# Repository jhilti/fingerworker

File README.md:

# Fingerworker

**[R31 mit Rev E in 3D ansehen →](https://fingerworker-development-notebook.jonashilti.chatgpt.site/#cad-r31-rev-e)** · [R20-3D-Archiv](https://jhilti.github.io/fingerworker/)

Ein 3D-gedruckter Prototyp für Fingerkrafttraining mit federgeführtem Griff, organischer Handballenauflage und optionaler Kraftmessung. Dieses Repository enthält CAD-Quellen, Firmware, eine iPhone-App, Elektronikentwurf und die Entwicklungshistorie.

*A 3D-printed finger-training prototype with a spring-loaded grip and optional force sensing. The latest documented assembly is Flat132 R31 with Rev E electronics.*

## R31 mit Rev‑E‑Elektronik

**Stand 25.11.2026.** Das vollständige R31-Modell zeigt den Federbetrieb in Ruhestellung mit flacher Handauflage, fester Sensorhaltnase, FX1901-Kraftsensor, Fingerschlitten, Akku und USB-C-Zugang von oben. Je ein verdrahteter Daumentaster sitzt links und rechts am Querbalken. Beide teilen sich den Eingang D7 über J4. Im iOS-Basistraining löst ein kurzer Druck einen Handwechsel aus.

Schaltplan- und Layoutprüfung in KiCad sowie Firmware- und iOS-Build sind abgeschlossen. Passung, Bediengefühl und Handwechsel per Bluetooth stehen am verdrahteten Muster noch zur Prüfung aus.

[Vollständige Baugruppe in Onshape](https://cad.onshape.com/documents/15316cc6370631845af136b2/w/8b79384f95b34ba58197ab08/e/061a7997871e238371c40026) · [Entwicklungsnotizbuch mit drehbarem 3D-Modell](https://fingerworker-development-notebook.jonashilti.chatgpt.site/#cad-r31-rev-e)

## Die App

Screenshots aus dem iOS-Simulator mit simulierten Testdaten.

| Training | Messung | Einstellungen |
| --- | --- | --- |
|  |  |  |
| Geführte Sätze und Handwechsel. | Kraftverlauf und Messwerte. | Trainingsart, Umfang und Pausen. |

## Modell ansehen

- **[R20-3D-Ansicht direkt öffnen](https://jhilti.github.io/fingerworker/)** – öffentliche interaktive Ansicht zum Teilen.
- [R20-3D-Ansicht als HTML](share/Fingerworker_R20_3D.html) – herunterladen und offline im Browser öffnen. GitHub zeigt die HTML-Datei auf der Repository-Seite als Quelltext an.
- [Projektübersicht](Uebersicht.html) – lokale Übersicht mit Modell und Dokumentation. Für ihre relativen Verweise das Repository herunterladen.
- [Onshape R20, unveränderliche Version](https://cad.onshape.com/documents/15316cc6370631845af136b2/v/0e06e3d98b9ecb574ee41402/e/d253eb87b70818ebde8215f0) – nativer CAD-Stand des R20-Releases.
- [Release v0.20.0-prototype](https://github.com/jhilti/fingerworker/releases/tag/v0.20.0-prototype) – native CAD-Downloads und Veröffentlichungsstand.

## Veröffentlichter Prototypstand R20

<!-- CURRENT_FLAT132_R20_START -->

Die hinteren Halter P06L und P06R sind separate massive Blöcke. Je ein integrierter **Ø5 × 2 mm Positionierzapfen** gleitet beim axialen Aufschieben in eine hinten offene Nut der Grundplatte. Das ermöglicht einen **federfreien, unbelasteten Passaufbau ohne Schrauben**. Die organische Handballenauflage, beidseitigen Daumenmulden und Durchlässe für zwei 25-mm-Gurte bleiben erhalten. Es gibt keine Vorspannverstellung.

**Vor jeder Federlast, auch der Vorspannung in Ruhestellung, sind vier M3×8-Schrauben in den vorgesehenen Inserts erforderlich.** Die Zapfen verriegeln die Blöcke nicht gegen Herausziehen. R20-Grundplatte und beide R20-Halter gemeinsam verwenden; [Montageanleitung beachten](review/rear-locating-pegs-2026-11-13/MONTAGE.md).

Nominale CAD-Prüfungen sind dokumentiert. Reale Druckpassung, Komfort, Elektronik, Kalibrierung und belastete Funktion bleiben zu prüfen. Es gibt keine validierte Lastfreigabe oder klinische Freigabe; frühere Kraftziele sind keine geprüften Belastbarkeitsangaben.

**Druckvorbereitung pausiert:** PLA ist das vorgesehene Standardmaterial. Für R20 existieren noch kein freigegebenes Bambu-Projekt und kein neuer Slice. Ältere Druckpakete bilden frühere Revisionen ab und enthalten die R20-Änderungen nicht.

<!-- CURRENT_FLAT132_R20_END -->

## CAD herunterladen

- [Native STL-Baugruppe: Flat132_R20_neutral_final.zip](https://github.com/jhilti/fingerworker/releases/download/v0.20.0-prototype/Flat132_R20_neutral_final.zip)
- [Native STEP-Baugruppe: Flat132_R20_final_AP214.step](https://github.com/jhilti/fingerworker/releases/download/v0.20.0-prototype/Flat132_R20_final_AP214.step)
- [FeatureScript-Quelle](fingerworker_mvp.fs) · [R20-Änderungsbericht](review/rear-locating-pegs-2026-11-13/README.md) · [Prüfbindung](review/rear-locating-pegs-2026-11-13/final-specification.json)

Die native STL-Baugruppe enthält auch Referenzhardware und ist kein fertig angeordnetes Druckprojekt. Für lokale Modell-Builds stellt der Download-Helfer das unveränderte ZIP am erwarteten Projektpfad wieder her:

```sh
python3 tools/download_release_assets.py
```

Details stehen in [Veröffentlichung und Wiederherstellung](PUBLISHING.md).

Weitere Downloads im selben Release:

- [R20-3D-Ansicht als ZIP](https://github.com/jhilti/fingerworker/releases/download/v0.20.0-prototype/Fingerworker_R20_3D.zip) – eigenständige HTML-Datei zum Weitergeben.
- [Historische Bambu-Projekte bis R18](https://github.com/jhilti/fingerworker/releases/download/v0.20.0-prototype/Historical_Bambu_Projects_through_R18.zip) – 24 bestehende 3MF-Dateien, ausschließlich historische Stände; **kein R20-Druckpaket**.
- [Historische Metallzeichnungen Rev A](https://github.com/jhilti/fingerworker/releases/download/v0.20.0-prototype/Historical_Mechanical_Drawings_RevA.zip).
- [Technische Elektronikexporte Rev A](https://github.com/jhilti/fingerworker/releases/download/v0.20.0-prototype/Electronics_RevA_Technical_Exports.zip) – dokumentierter Entwicklungsstand, keine Fertigungsfreigabe.

## Projektbereiche

| Bereich | Inhalt |
| --- | --- |
| [Mechanik und Montage](review/rear-locating-pegs-2026-11-13/README.md) | R20-Geometrie, Positionierzapfen, Passungen und nominale Prüfungen |
| [Stückliste](EINKAUFSTEILE.md) | Bauteile, Befestigungen und Revisionshinweise |
| [Firmware](firmware/README.md) | Kraftmessung, Endschalter, BLE und lokale Test-/Build-Werkzeuge |
| [iPhone-App](ios/README.md) | BLE-Anbindung, Trainingsansicht und Sitzungsspeicherung |
| [Elektronik](electronics/kicad/README.md) | KiCad-Schaltplan, Platine und dokumentierter Entwurfsstand |
| [Spezifikation](SPECIFICATION.md) / [offene Arbeiten](GAP_ANALYSIS.md) | Anforderungen und noch ausstehende Hardware-Nachweise |
| [Druckstatus](print/REVISION_STATUS.md) | Zuordnung früherer Druckstände; R20-Druckvorbereitung pausiert |

Firmware, App und Elektronik sind Teil des Prototyps. Eine dokumentierte Softwareprüfung ersetzt keine elektrische oder mechanische Qualifikation des aufgebauten Geräts. Bei historischen Dokumenten gilt die jeweils genannte Revision.

## Umfang der Veröffentlichung

Quellen und technische Entwicklungshistorie bleiben erhalten. Persönliche Bestellungen und Scans, Studien mit persönlichen Referenzen, Laufzeitumgebungen, Hersteller-PDFs/-CAD sowie alte generierte Spiegelkopien sind aus dem öffentlichen Repository ausgenommen. Historische Dokumente können deshalb auf nur lokal vorhandene Dateien verweisen. Details und CAD-Wiederherstellung stehen in [PUBLISHING.md](PUBLISHING.md).

Für die eigenen Projektdateien wurde noch keine Open-Source-Lizenz gewählt. Die Veröffentlichung allein erteilt keine solche Lizenz; gegebenenfalls enthaltene Drittbestandteile behalten ihre jeweiligen Lizenzbedingungen.

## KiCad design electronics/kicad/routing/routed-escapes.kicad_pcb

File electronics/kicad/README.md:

# Fingerworker – KiCad, Revision A

11. Oktober 2026. **Geroutetes, editierbares Prototypenprojekt Rev A-P1 für KiCad 10.0.6**, abgeglichen mit `electronics/order/RevA-P1-JLC/source/`. C4 und C7: jeweils **22 µF**, Murata **GRM21BR61E226ME44L**, 25 V, X5R, 0805. Schaltpläne, PCB, lokale Symbolbibliothek und native Pin-/Netzdaten entsprechen dieser eingefrorenen JLC-Quelle. Routing und Bauteilpositionen sind unverändert.

Die separat freigegebenen YAGEO-Ersatzteile für C5/C6/C13 bleiben im JLC-Portal-BOM und in `../order/RevA-P1-JLC/SUBSTITUTIONS.md` dokumentiert; die eingefrorene Quell-BOM enthält deren ursprüngliche Murata-MPNs. Für Portal-Uploads gilt `BOM_JLC_portal.csv`.

Frische ERC-/DRC-Prüfung einschließlich Schaltplanabgleich: keine Fehler, Warnungen oder offenen Verbindungen. Hardwarefunktion und Gehäuseintegration bleiben am Muster zu prüfen. USB-Erkennung der Firmware verwendet jetzt den internen VBUS-Detektor statt des D6-Teilers.

## Öffnen

`Fingerworker_RevA.kicad_pro` in KiCad öffnen; Schaltplan und PCB über den Projektmanager starten. Symbol- und Footprint-Bibliotheken sind lokal enthalten. Unter `preview/` liegen alle vier Schaltplanblätter, beide PCB-Seiten und die lokale Bauraumstudie als SVG/PNG.

## Platine

- **19,5 × 68,5 × 0,8 mm**, vier Kupferlagen, ausschließlich Bestückung oben.
- 48 Footprints, 51 Schaltplansymbole einschließlich externem Sensor, Akku und Endschalter.
- F.Cu: Bauteile, kurze Mess- und Schaltreglerwege. In1.Cu: zusammenhängende Massefläche ohne Signalleiterbahnen. In2.Cu und B.Cu: weitere Verbindungen und ergänzende Masseflächen.
- Der Antennenbereich und der angrenzende Freiraum sind auf **allen vier Kupferlagen** gesperrt. Funkleistung mit Hand und Gehäuse bleibt zu messen.
- Boost-Schaltknoten, Rückstromschleife, ADC-Abblockung und Eingangsfilter wurden gezielt angeordnet und geroutet. Die getrennten Erregungs-Sense-Leitungen enden direkt an J2: Net-Ties 1–5 und 4–6. Physisch bleiben vier Sensoradern; Spannungsabfälle im Sensorkabel werden damit nicht kompensiert.
- 0,15 mm Mindestabstand/-leiterbahnbreite, 0,25 mm Kupfer–Rand, ausschließlich 0,6/0,3-mm-Durchkontaktierungen. Versorgungswege überwiegend 0,4 mm; lokale ADC-Anschlüsse sind schmaler. Den 0,8-mm-Vierlagenaufbau mit dem späteren Fertiger festlegen.
- Die XIAO-Lands haben nominell 0,2925 mm Abstand zum PCB-Rand. Ihre Geometrie entspricht der Herstellerbibliothek.

Vier Lagen erlauben eine eigene Massefläche unter der Messschaltung bei unveränderter Platinenstärke. Die frühere zweilagige Platzierung ist im Arbeitsverzeichnis archiviert.

## Prüfungen

| Prüfung | Ergebnis |
|---|---:|
| Native Schaltplannetze gegen Pin-/Netzdaten | 140 verbundene + 10 explizit unbenutzte Pins, 0 Abweichungen |
| ERC | 0 Fehler / Warnungen |
| DRC inklusive gefüllter Kupferflächen | 0 Fehler / Warnungen |
| Offene Verbindungen | **0** |
| Schaltplan–PCB-Abgleich | 0 Abweichungen |
| Masse-Innenlage | 1 verbundene Fläche, keine Signalleiterbahnen |

Berichte: `reports/verification-summary.json`, `erc-full-review.json`, `drc-full-review.json`, `full-review-netlist.xml`. Keine DRC-Verletzungen als Ausnahmen ausgeblendet. Diese Prüfungen belegen Netztreue und geometrische Regeln, keine gemessene Funktion, Funkleistung oder mechanische Belastbarkeit.

## Einbau

Die lokale FeatureScript-Bauraumstudie verwendet jetzt die tatsächlichen PCB-Positionen und Courtyards. Das Elektronikgehäuse ist nominell **22,5 × 110 × 8,9 mm**, mit 0,5 mm Platinenspiel pro Seite und 0,35 mm Reserve über dem 5,5-mm-JST plus 0,15-mm-Lötzugabe. Die Platine sitzt 0,3 mm über dem Boden; zur festen Handballenplatte bleiben 0,6 mm. Die Gerätehöhe bleibt 30 mm.

Der Akku wurde innerhalb der Studie um 3 mm verschoben; hinten bleibt 1 mm. Gegenstecker/Leitungsansatz und Seitentaster haben eigene Hüllkörper und Zugangsöffnungen. 51 Komponenten-/PCB-/Akku-Hüllkörper passen nominal in den reservierten Innenraum. Darstellung: `preview/mechanical-fit.svg`; Maße und Grenzen: `reports/mechanical-fit-local.json`.

**In Onshape aktualisiert und geprüft:** Bei 0/15/30 mm Hub mit Handmodell jeweils 43 ausgewählte Körperpaare ohne Volumenüberschneidung; alle sieben Elektronik-Prüfpaare CLEAR. Der kleinste Gehäuse-/Mechanikabstand ist von 0,1 auf **0,6 mm** vergrößert; Drucktoleranzen und belastete Verformung bleiben zu prüfen. Die Elektronik bleibt mindestens 4,70 mm vom Handmodell entfernt. Aktuelle Berichte liegen unter `../../review/` im Arbeitsverzeichnis und im neuen Vollreview-Paket. Die früheren Berichte gelten nur für die alte Studie. Die neue lokale Studie ist kein druckfertiges Gehäuse; XIAO-Höhe, Gegenstecker und Tasterbetätigung enthalten Planungsreserven. Die KiCad-3D-Bibliotheken sind für U1/J1/L1 unvollständig; eine 3D-Ansicht allein ist kein Einbaunachweis.

## Endschalter nach Vollreview

**NC statt NO:** NC an J3.1, COM an J3.2; NO isolieren. `ENDSTOP_N` (D5/P0.05) ist LOW bei Endlage oder unterbrochener Leitung. Bei V5A aus ungültig. Die Kupferführung ist unverändert; Schaltplan, Bibliothek, Netznamen und Verbindungsliste sind aktualisiert. Kraftwerte am Hartanschlag sind wegen Lastbypass nicht vollständig; Firmware muss sie entsprechend sperren. Siehe `../FIRMWARE_CONTRACT.md` (im neuen Paket unter `electronics/`).

## Vor Bestellung

1. Vorhandenen Akku-Kabelbaum messen: J1 ist hier **1 = VBAT, 2 = GND**; tatsächliche Steckerpolarität bestätigen.
2. Konkrete Passiv-MPNs und effektive MLCC-Kapazitäten festlegen. Lieferbares Vierlagen-Stackup und Fertigungstoleranzen bestätigen.
3. Sensor-Gleichtakt, Boost-Ripple, monotone ADC-Versorgungsrampen, Ladestrom/Temperatur und Kalibrierung am Tischaufbau prüfen. Die offenen elektrischen Punkte aus `../README.md` bleiben relevant.
4. 0,6-mm-Gehäuse-/Mechanikspalt gegen Drucktoleranzen und Verformung prüfen. Tatsächlichen Modulstapel, Gegenstecker/Kabelbiegung, Akkuhalterung, Zugentlastung und Befestigung auslegen. Anschließend die Kollisionsprüfung wiederholen.

Gerber-/Bohr-/Bestückungsdaten sind noch nicht freigegeben. Die PCB-Datei enthält alle gerouteten Daten für den weiteren Review.

## Quellen und Bearbeitung

- Herstellergeometrie: [Seeed XIAO](https://wiki.seeedstudio.com/XIAO_BLE/), [JST PH, SMT side entry 5,5 mm](https://www.jst-mfg.com/product/pdf/eng/ePH.pdf), [Coilcraft XFL3012](https://www.coilcraft.com/en-us/products/power/shielded-inductors/molded-inductor/xfl/xfl3012/). Weitere elektrische Quellen stehen in `../README.md`.
- KiCad-Standard-Footprints 10.0.6 sowie lokale Herstellerkopien. XIAO-Kupfergeometrie unverändert; dekorative Umrisse auf F.Fab. J2 enthält die beiden zusätzlichen internen Sense-Net-Ties.
- Das native Projekt ist der bearbeitbare Lieferstand. Entwicklungsskripte im Arbeitsverzeichnis erzeugen Zwischenstände und können Dateien überschreiben. `build_pcb.py` erzeugt nur die historische Platzierung; es verweigert jetzt das Überschreiben einer gerouteten Platine ohne ausdrückliches Flag. Auch `build_kicad.py` verweigert das ungefragte Überschreiben der geprüften Schaltpläne und Bibliotheken.
- `verify_project.py` führt ERC, DRC und Netzlistenexport frisch aus. Es prüft alle vorgesehenen Pins einschließlich NC sowie die PCB-Padnetze; zusätzliche Pins werden nicht mehr stillschweigend herausgefiltert. Eingaben und Berichte sind per SHA-256 gebunden. Ein fehlgeschlagener Lauf hinterlässt kein altes PASS-Ergebnis. `update_packaging.py` erzeugt die lokale Hüllkörperstudie; `review_packaging.py` prüft deren nominelle Innenraummaße. Die separate Onshape-Prüfung ist an den übertragenen FeatureScript-Quellstand gebunden; Änderungen benötigen neue Prüfungen.

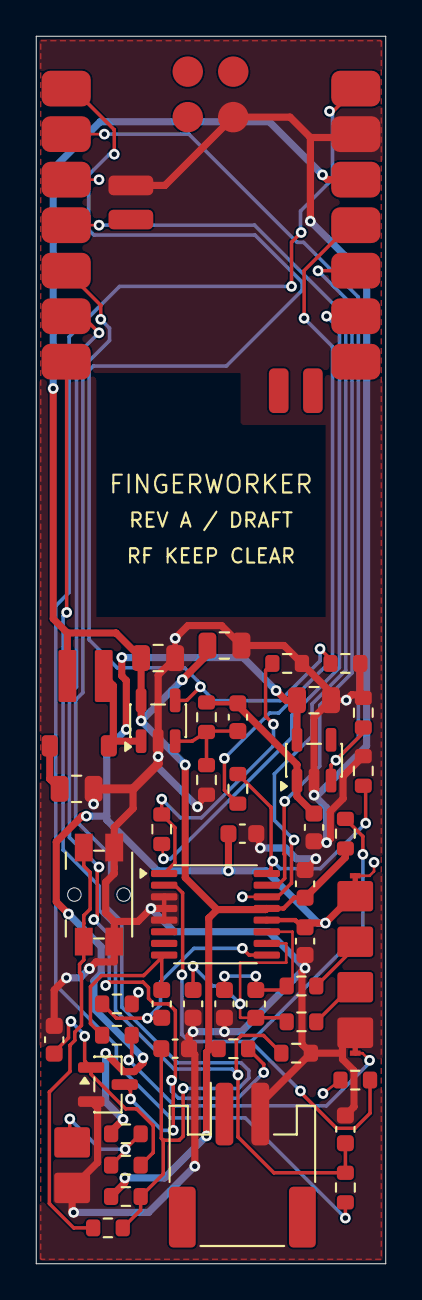
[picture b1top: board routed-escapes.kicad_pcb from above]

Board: 2 copper layers, 19.5 x 68.5 mm, 48 parts (0 on the bottom side), 32 nets.

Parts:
C1, C3, C4: 10 uF; C_0805_2012Metric
C2: 10 nF; C_0603_1608Metric
C5: 47 pF; C_0603_1608Metric
C6, C13: 1 uF; C_0603_1608Metric
C7: 4.7 uF; C_0805_2012Metric
C8: 470 nF; C_0603_1608Metric
C9, C10: 4.7 nF; C_0603_1608Metric
C11, C12, C14, C15, C16: 100 nF; C_0603_1608Metric
D1: MBR0520LT1G; D_SOD-123
J1: JST_PH_2; JST_PH_S2B-PH-SM4-TB_1x02-1MP_P2.00mm_Horizontal
J2: FORCE_4; SolderWire_4x2mm_P2.54
J3: END_2; SolderWire_2x2mm_P2.54
L1: 10 uH; L_Coilcraft_XFL3012
Q1: 2N7002; SOT-23
R1, R2, R5, R6, R15, R16, R20: 100 k; R_0603_1608Metric
R3: 680 k; R_0603_1608Metric
R4: 200 k; R_0603_1608Metric
R7, R8, R18, R21: 1 k; R_0603_1608Metric
R9, R10: 100 R; R_0603_1608Metric
R11, R12, R13: 33 R; R_0603_1608Metric
R14, R19: 47 k; R_0603_1608Metric
R17: 4.7 k; R_0603_1608Metric
SW2: EVQPUC02K; Panasonic_EVQPUL_EVQPUC
U1: XIAO_nRF52840; Seeed_XIAO_nRF52840_SMD
U2: TPS61041DBVR; SOT-23-5
U3: TPS7A2050PDBVR; SOT-23-5
U4: ADS1220IPWR; TSSOP-16_4.4x5mm_P0.65mm

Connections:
ADC_CS_MCU: R13.1, U1.3
ADC_CS_N: R13.2, R14.2, U4.2
ADC_DRDY_N: U1.4, U4.14
AIN_N: C8.2, C10.1, R8.2, U4.10
AIN_P: C8.1, C9.1, R7.2, U4.11
ANALOG_EN: R6.1, U1.2, U3.3
BOOST_EN: R5.1, U1.1, U2.4
BOOST_FB: C5.2, R3.2, R4.1, U2.3
BOOST_SW: D1.2, L1.2, U2.1
BUTTON_N: C16.1, R20.2, R21.2, U1.5
BUTTON_RAW: R21.1, SW2.1
END_ACTIVE: Q1.3, R19.2, U1.6
END_CONTACT: J3.1, R17.2, R18.1
END_GATE: C15.1, Q1.1, R18.2
EXC_SENSE_N: J2.6, R10.1
EXC_SENSE_P: J2.5, R9.1
GND: C1.2, C2.2, C3.2, C4.2, C6.2, C7.2, C9.2, C10.2, C12.2, C13.2, C14.2, C15.2, C16.2, J1.2, J2.4, J3.2, Q1.2, R2.2, R4.2, R5.2, R6.2, R15.2, R16.2, SW2.2, U1.13, U1.18, U1.20, U2.2, U3.2, U4.3, U4.4, U4.5
REF_N: C11.2, R10.2, U4.8
REF_P: C11.1, R9.2, U4.9
SIG_N: J2.3, R8.1
SIG_P: J2.2, R7.1
SPI_MISO: U1.10, U4.15
SPI_MOSI_ADC: R12.2, R16.1, U4.16
SPI_MOSI_MCU: R12.1, U1.11
SPI_SCK_ADC: R11.2, R15.1, U4.1
SPI_SCK_MCU: R11.1, U1.9
USB_PRESENT: C2.1, R1.2, R2.1, U1.7
V3V3: C1.1, C3.1, C14.1, L1.1, R14.1, R19.1, R20.1, U1.12, U2.5, U4.13
V5A: C7.1, C12.1, C13.1, J2.1, R17.1, U3.5, U4.12
VBAT: J1.1, U1.19
VBOOST: C4.1, C5.1, C6.1, D1.1, R3.1, U3.1
VBUS_USB: R1.1, U1.14

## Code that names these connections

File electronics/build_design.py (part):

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assert all(len(nodes)>=2 for nodes in nets.values()), 'Unintended one-pin net'

# Independent electrical envelope and pin checks, not SPICE/ERC.
assert byref['U4']['pins']['12']['net']=='V5A'
assert byref['U4']['pins']['13']['net']=='V3V3'
assert byref['U4']['pins']['9']['net']=='REF_P'
assert byref['U4']['pins']['8']['net']=='REF_N'
assert byref['Q1']['pins']['3']['net']=='ENDSTOP_N'
assert byref['U1']['pins']['6']['net']=='ENDSTOP_N'
assert not any(n['ref']=='U1' for n in nets['V5A'])
assert {n['ref'] for n in nets['VBAT']}=={'BT1','J1','U1'}
assert byref['U3']['pins']['3']['net']=='ANALOG_EN'
ratio=680e3/200e3
vboost=1.233*(1+ratio)
vboost_min=1.208*(1+ratio*.999/1.001)
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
